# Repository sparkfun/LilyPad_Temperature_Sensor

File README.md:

LilyPad Temperature Sensor
========================================

[*LilyPad Temperature Sensor (DEV-08777)*](https://www.sparkfun.com/products/8777)

Detecting temperature changes has never been easier. 
The MCP9700 is a small thermistor type temperature sensor. 
This sensor will output 0.5V at 0 degrees C, 0.75V at 25 C, and 10mV per degree C. Doing an analog to digital conversion on the signal line will allow you to establish the local ambient temperature. 
Detect physical touch based on body heat and ambient conditions with this small sensor.

Repository Contents
-------------------
* **/Firmware** - Arduino Example code 
* **/Hardware** - Eagle design files (.brd, .sch)
* **/Production** - Production panel files (.brd)

Documentation
--------------
* **[Hookup Guide](https://learn.sparkfun.com/tutorials/lilypad-temperature-sensor-hookup-guide)** - Basic Hookup Guide for the LilyPad temperature sensor.
* **[SparkFun Fritzing repo](https://github.com/sparkfun/Fritzing_Parts)** - Fritzing diagrams for SparkFun products.
* **[SparkFun 3D Model repo](https://github.com/sparkfun/3D_Models)** - 3D models of SparkFun products. 

License Information
-------------------
This product is _**open source**_! 

The **hardware** is released under [Creative Commons ShareAlike 4.0 International](https://creativecommons.org/licenses/by-sa/4.0/).

Please use, reuse, and modify these files as you see fit. Please maintain attribution to SparkFun Electronics and release anything derivative under the same license.

Distributed as-is; no warranty is given.

- Your friends at SparkFun.

_**Note:** A portion of this sale is given back to Dr. Leah Buechley for continued development and education of e-textiles._

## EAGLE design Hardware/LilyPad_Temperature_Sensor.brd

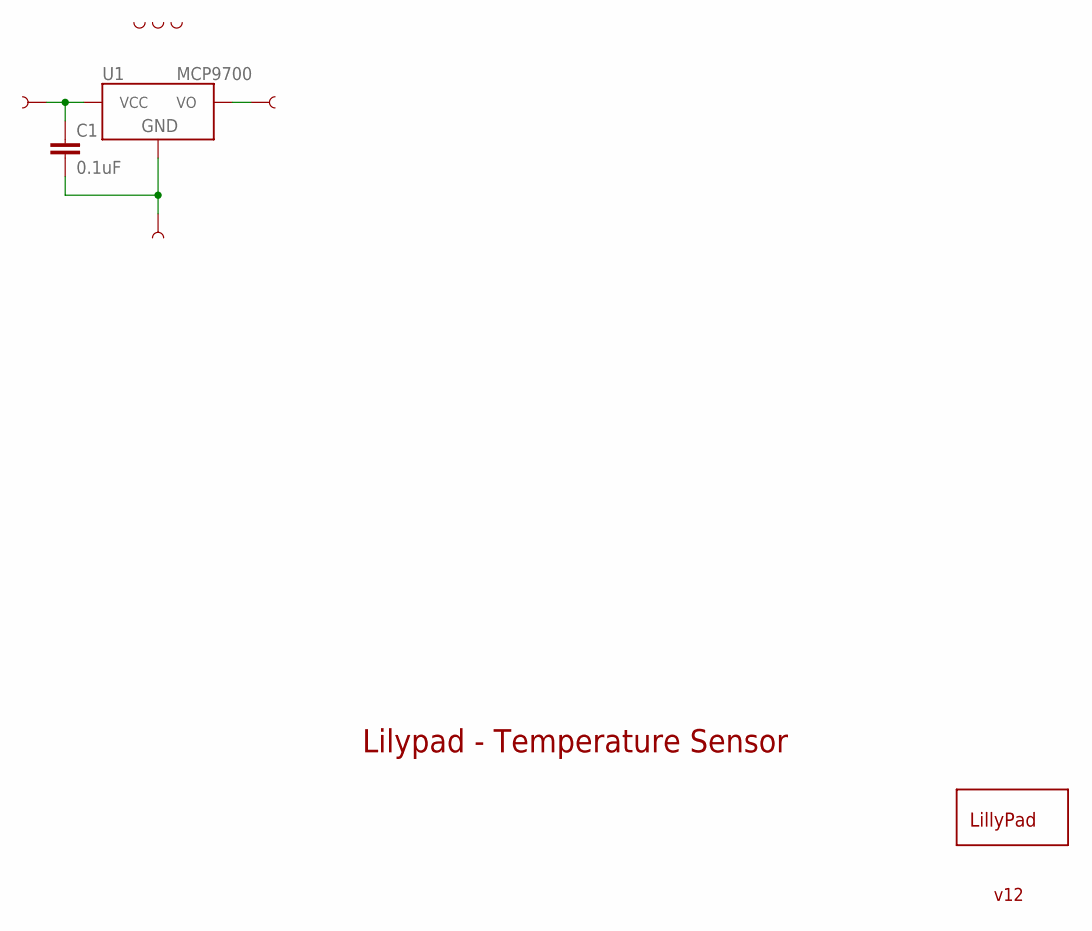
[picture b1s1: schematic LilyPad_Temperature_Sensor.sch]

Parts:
C1: 0.1uF; 0603-CAP
TEMP1, TEMP2, TEMP3: SEWTAP-NOHOLE2; PETAL-NOHOLE-2SIDE
TEMP+: SEWTAP6; PETAL-SMALL-2SIDE
TEMP-: SEWTAP6; PETAL-SMALL-2SIDE
TEMPS: SEWTAP6; PETAL-SMALL-2SIDE
U1: MCP9700; SOT23-3
U$2: LOGO-LPLP; LOGO-LILYPAD

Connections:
GND: C1.2, TEMP-.1, U1.3 (GND)
VCC: C1.1, TEMP+.1, U1.1 (VCC)
VO: TEMPS.1, U1.2 (VO)

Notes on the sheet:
Lilypad - Temperature Sensor
v12

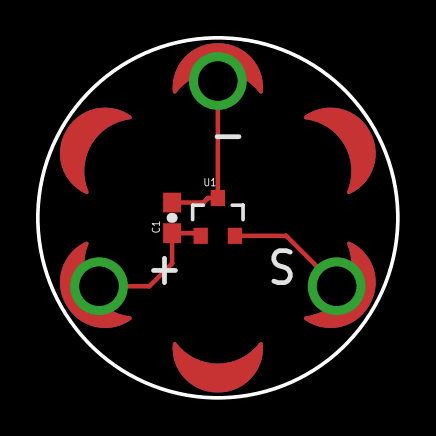
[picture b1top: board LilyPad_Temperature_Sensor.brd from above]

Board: 2 copper layers, 20.0 x 20.0 mm, 9 parts (1 on the bottom side), 3 nets.

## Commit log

2015-05-05 Hardware files commited
2018-01-23 Create ReadTemperature.ino
    Adding Angela's Example Code
2018-01-23 Create ThermalTrigger.ino
    Adding Angela's Example Code.
2018-01-23 Update README.md
    Linking Hookup Guide.
